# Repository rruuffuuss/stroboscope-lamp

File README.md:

This repo contains artefacts for a stroboscope I designed inspired by an exhibition I saw at the [Museum of Illusions Budapest](https://illuziokmuzeuma.hu/en/). I wanted to design a stroboscope with internal light and synchronisation such that no manual rotation speed or strobe frequency adjustment is required, and no strobe light or motor is visible.

The premise is that a geometrically designed translucent platter spins on an electric motor at a precise speed, synchronised using magnets in the platter and a hall effect sensor in the base. LED strips underneath the platter then strobe above the [flicker fusion threshold](https://en.wikipedia.org/wiki/Flicker_fusion_threshold) of human eyesight, such that the geometry in the platter appears to morph and twist in an impossible manner.

In the off chance someone is actually interested in making this, or something similar, please get in contact and I will dig out a bill of materials I used in a final version.
Whilst this prototype does "work" (i.e. succeeds in the tricking the eye into seeting hovering shapes morphing and twisting), it could be executed far better with a higher RPM, quieter motor, and more attention to detail.

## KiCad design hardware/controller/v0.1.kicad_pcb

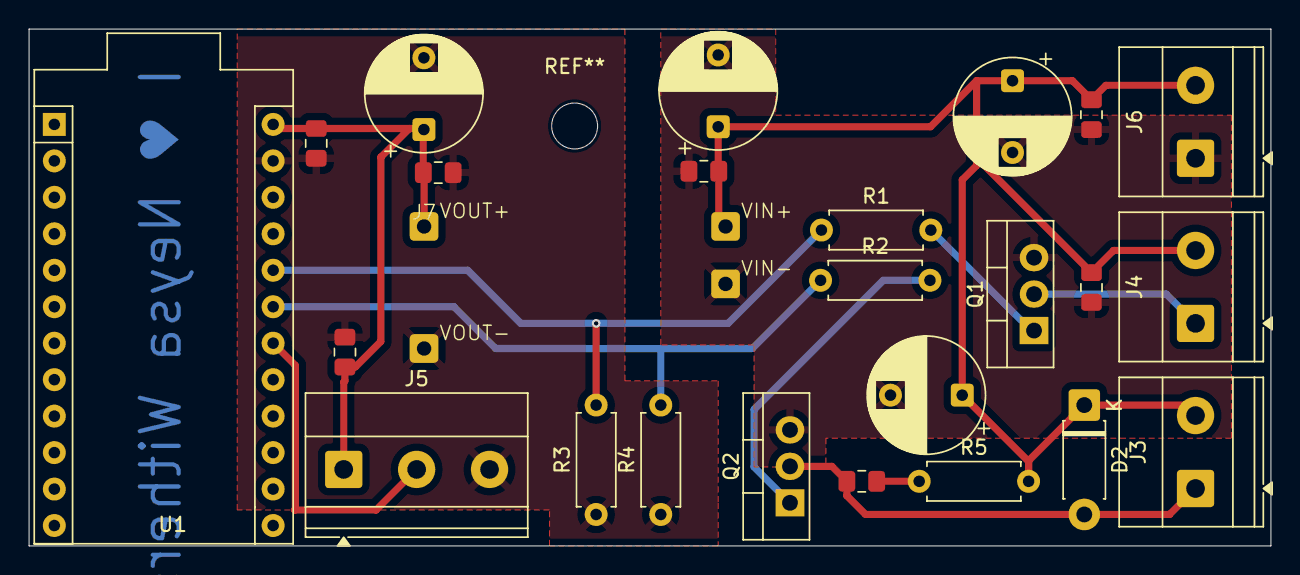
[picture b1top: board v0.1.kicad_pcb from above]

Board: 2 copper layers, 86.5 x 36.0 mm, 25 parts (0 on the bottom side), 12 nets.

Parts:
C_12V_100n_a1: 0.1 µF; C_0805_2012Metric_Pad1.18x1.45mm_HandSolder
C_12V_bulk1: 100 µF; CP_Radial_D8.0mm_P5.00mm
C_BUCK_IN_100n1: 0.1 µF; C_0805_2012Metric_Pad1.18x1.45mm_HandSolder
C_BUCK_IN_bulk1: 100 µF; CP_Radial_D8.0mm_P5.00mm
C_BUCK_OUT_100n1: 0.1 µF; C_0805_2012Metric_Pad1.18x1.45mm_HandSolder
C_BUCK_OUT_bulk1: 100 µF; CP_Radial_D8.0mm_P5.00mm
C_HALL_100n1: 0.1 µF; C_0805_2012Metric_Pad1.18x1.45mm_HandSolder
C_LED_IN_100n1: 0.1 µF; C_0805_2012Metric_Pad1.18x1.45mm_HandSolder
C_MOTOR_bulk1: 100 µF; CP_Radial_D8.0mm_P5.00mm
C_MOTOR_snub1: 0.1 µF; C_0805_2012Metric_Pad1.18x1.45mm_HandSolder
C_PM_100n1: 0.1 µF; C_0805_2012Metric_Pad1.18x1.45mm_HandSolder
D2: 1N5819; D_DO-41_SOD81_P7.62mm_Horizontal
J3, J4, J6: Screw_Terminal_01x02; TerminalBlock_Phoenix_MKDS-1,5-2-5.08_1x02_P5.08mm_Horizont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
J5: Screw_Terminal_01x03; TerminalBlock_Phoenix_MKDS-1,5-3-5.08_1x03_P5.08mm_Horizont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
J7: 12v_5v_BUCK; BuckConverter_Header_1x04_Custom
Q1, Q2: IRL540N; TO-220-3_Vertical
R1, R2: 220; R_Axial_DIN0207_L6.3mm_D2.5mm_P7.62mm_Horizontal
R3, R4: 10k; R_Axial_DIN0207_L6.3mm_D2.5mm_P7.62mm_Horizontal
R5: 100 Ω; R_Axial_DIN0207_L6.3mm_D2.5mm_P7.62mm_Horizontal
U1: Sparkfun_Pro_Micro

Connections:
/+5V: C_BUCK_OUT_100n1.2, C_BUCK_OUT_bulk1.1, C_HALL_100n1.2, C_PM_100n1.2, J5.1, J7.1, U1.24 (RAW)
/+12V: C_12V_100n_a1.2, C_12V_bulk1.1, C_BUCK_IN_100n1.2, C_BUCK_IN_bulk1.1, C_LED_IN_100n1.2, C_MOTOR_bulk1.1, D2.1 (K), J3.2, J4.2, J6.2, J7.3, R5.2
/GND1: C_12V_100n_a1.1, C_12V_bulk1.2, C_BUCK_IN_100n1.1, C_BUCK_IN_bulk1.2, C_LED_IN_100n1.1, C_MOTOR_bulk1.2, J6.1, J7.4, Q1.3 (S), Q2.3 (S)
/GND2: C_BUCK_OUT_100n1.1, C_BUCK_OUT_bulk1.2, C_HALL_100n1.1, C_PM_100n1.1, J5.3, J7.2, R3.1, R4.1, U1.23 (GND)
/LED_CTRL: R1.1, R3.2, U1.20 (D21/A3)
/MOTOR_CTRL: R2.1, R4.2, U1.19 (D20/A2)
/SNSR_READ: J5.2, U1.18 (D19/A1)
unnamed: C_MOTOR_snub1.1, R5.1
unnamed: C_MOTOR_snub1.2, D2.2 (A), J3.1, Q2.2 (D)
unnamed: J4.1, Q1.2 (D)
unnamed: Q1.1 (G), R1.2
unnamed: Q2.1 (G), R2.2

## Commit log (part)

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2025-07-20 cad: record platter.stl export
2025-07-26 cad: record platter (1).stl export
2025-07-26 cad: record stand.stl export
2025-07-27 cad: record Base 2.0.stl export
2025-07-29 cad: record platter final.stl export
2025-07-30 cad: record HollowPlatter.stl export
2025-08-06 hardware: record saved PCB layout
2025-08-06 hardware: vendor g200kg Arduino KiCad library with its CC0 license
2025-08-18 hardware: record saved footprint library table
2025-08-18 hardware: record saved custom footprint
2025-08-19 hardware: record saved KiCad project state
2025-08-22 hardware: record saved schematic
2025-08-23 hardware: record initial August 23 fabrication export
2025-08-23 hardware: retain 2025-08-23-drill-package manufacturing package
2025-08-23 hardware: retain 2025-08-23-package manufacturing package
2025-08-24 hardware: record PCB assembly STEP export
2025-08-31 hardware: record August 31 fabrication export
2025-08-31 hardware: retain 2025-08-31 manufacturing package
2025-08-31 cad: record platterp0.1.stl export
2025-09-02 cad: record platterp0.3.stl export
2025-09-03 cad: record frame_02.stl export
2025-09-23 cad: record Frame0.3.stl export
2025-09-25 cad: record FrameV0.4.stl export
2025-09-25 firmware: record Hall sensor serial test on pin 27
2025-09-25 firmware: retain commented LED experiment
2025-09-25 firmware: retain commented Hall sensor experiment
2025-09-28 cad: record FrameV05.stl export
2025-09-28 cad: record FrameV06.stl export
2025-09-28 cad: record FrameV07.stl export
2025-10-13 firmware: record motor and strobe controller
